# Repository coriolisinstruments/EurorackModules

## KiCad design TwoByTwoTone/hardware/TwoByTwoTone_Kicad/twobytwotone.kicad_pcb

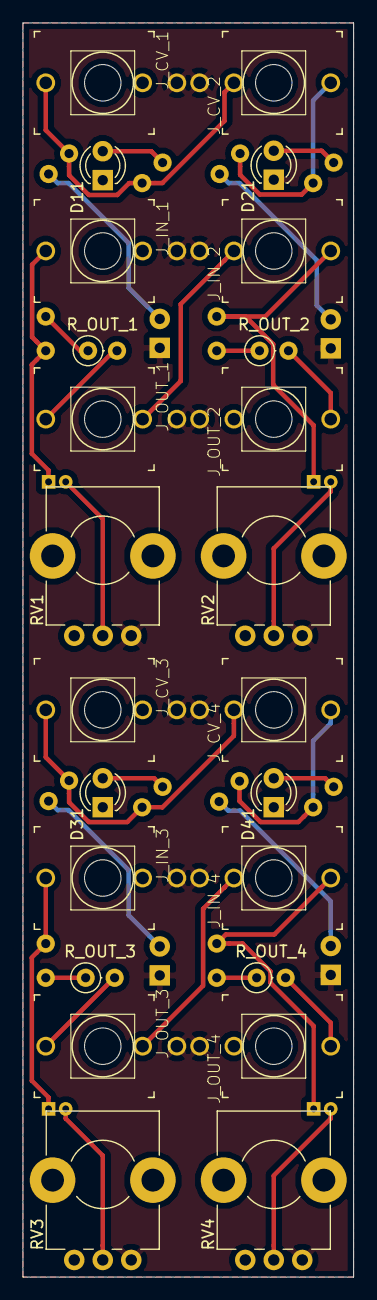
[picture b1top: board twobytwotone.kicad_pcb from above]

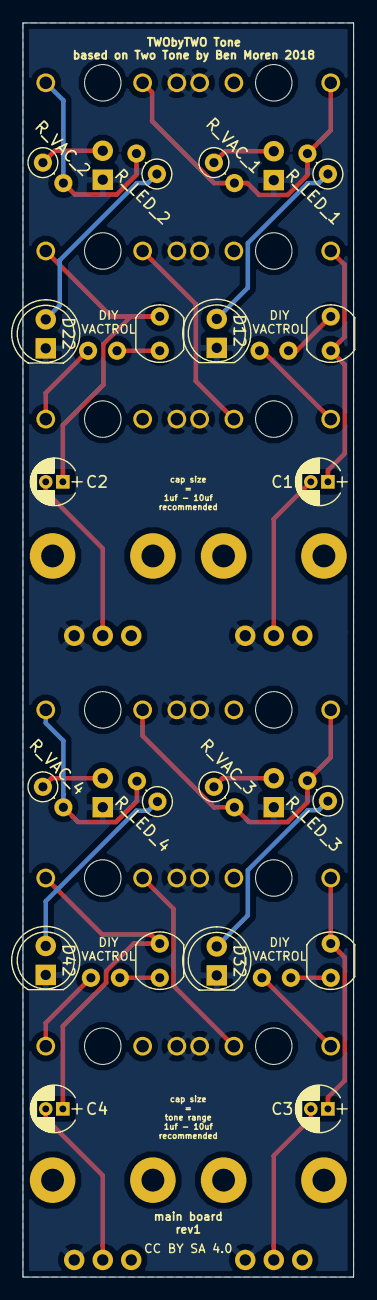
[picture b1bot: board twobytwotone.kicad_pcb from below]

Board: 2 copper layers, 29.0 x 110.0 mm, 44 parts (20 on the bottom side), 31 nets.

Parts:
C1, C2, C3, C4: 10uF; CP_Radial_D4.0mm_P1.50mm
D11, D21, D31, D41: LED; LED_D3.0mm
D12, D22, D32, D42: VAC-LED; LED_D5.0mm
J_CV_1, J_CV_2, J_CV_3, J_CV_4: thonkiconn; MusicThingModular-WQP-PJ301M-12_JACK
J_IN_1, J_IN_2, J_IN_3, J_IN_4: thonkiconn; MusicThingModular-WQP-PJ301M-12_JACK
J_OUT_1, J_OUT_2, J_OUT_3, J_OUT_4: thonkiconn; MusicThingModular-WQP-PJ301M-12_JACK
RV1, RV2, RV3, RV4: A10K; Potentiometer_Alps_RK09K_Horizontal
R_LED_1, R_LED_2, R_LED_3, R_LED_4: 20K; R_Axial_DIN0207_L6.3mm_D2.5mm_P2.54mm_Vertical
R_OUT_1, R_OUT_2, R_OUT_3, R_OUT_4: 1K; R_Axial_DIN0207_L6.3mm_D2.5mm_P2.54mm_Vertical
R_VAC_1, R_VAC_2, R_VAC_3, R_VAC_4: 20K; R_Axial_DIN0207_L6.3mm_D2.5mm_P2.54mm_Vertical
VAC-PHOTO1, VAC-PHOTO2, VAC-PHOTO3, VAC-PHOTO4: 45k-140k1; Resistor_LDR_5x4.1_RM3

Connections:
GND: D11.1, D12.1, D21.1, D22.1, D31.1, D32.1, D41.1, D42.1, J_CV_1.P$3_SLEEVE, J_CV_2.P$3_SLEEVE, J_CV_3.P$3_SLEEVE, J_CV_4.P$3_SLEEVE, J_IN_1.P$3_SLEEVE, J_IN_2.P$3_SLEEVE, J_IN_3.P$3_SLEEVE, J_IN_4.P$3_SLEEVE, J_OUT_1.P$3_SLEEVE, J_OUT_2.P$3_SLEEVE, J_OUT_3.P$3_SLEEVE, J_OUT_4.P$3_SLEEVE, RV1.1, RV2.1, RV3.1, RV4.1
unnamed: C1.1, J_IN_1.P$1_TIP, VAC-PHOTO1.1
unnamed: C1.2, RV1.2
unnamed: C2.1, J_IN_2.P$1_TIP, VAC-PHOTO2.2
unnamed: C2.2, RV2.2
unnamed: C3.1, J_IN_3.P$1_TIP, VAC-PHOTO3.2
unnamed: C3.2, RV3.2
unnamed: C4.1, J_IN_4.P$1_TIP, VAC-PHOTO4.2
unnamed: C4.2, RV4.2
unnamed: D11.2, R_VAC_1.1
unnamed: D12.2, R_LED_1.1
unnamed: D21.2, R_VAC_2.1
unnamed: D22.2, R_LED_2.1
unnamed: D31.2, R_VAC_3.1
unnamed: D32.2, R_LED_3.1
unnamed: D41.2, R_VAC_4.1
unnamed: D42.2, R_LED_4.1
unnamed: J_CV_1.P$1_TIP, J_CV_2.P$2_SWITCH, R_LED_1.2, R_VAC_1.2
unnamed: J_CV_2.P$1_TIP, R_LED_2.2, R_VAC_2.2
unnamed: J_CV_3.P$1_TIP, J_CV_4.P$2_SWITCH, R_LED_3.2, R_VAC_3.2
unnamed: J_CV_4.P$1_TIP, R_LED_4.2, R_VAC_4.2
unnamed: J_IN_2.P$2_SWITCH, J_OUT_1.P$2_SWITCH
unnamed: J_IN_4.P$2_SWITCH, J_OUT_3.P$2_SWITCH
unnamed: J_OUT_1.P$1_TIP, R_OUT_1.2
unnamed: J_OUT_2.P$1_TIP, R_OUT_2.2
unnamed: J_OUT_3.P$1_TIP, R_OUT_3.2
unnamed: J_OUT_4.P$1_TIP, R_OUT_4.2
unnamed: R_OUT_1.1, VAC-PHOTO1.2
unnamed: R_OUT_2.1, VAC-PHOTO2.1
unnamed: R_OUT_3.1, VAC-PHOTO3.1
unnamed: R_OUT_4.1, VAC-PHOTO4.1

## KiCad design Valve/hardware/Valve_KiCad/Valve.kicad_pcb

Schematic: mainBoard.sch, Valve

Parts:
C1, C2: 47nF; C_Rect_L7.0mm_W2.5mm_P5.00mm
C3, C4, C10: 10uF (25V); CP_Radial_D4.0mm_P2.00mm
C5, C6, C9: 100nF; C_Rect_L7.0mm_W2.5mm_P5.00mm
C7: 1uF (25V); CP_Radial_D4.0mm_P2.00mm
C8: 10nF; C_Rect_L7.0mm_W2.5mm_P5.00mm
D1, D2: IN4001; D_DO-41_SOD81_P10.16mm_Horizontal
D3, D4, D5: IN4148; D_DO-35_SOD27_P7.62mm_Horizontal
D6: LED; LED_D3.0mm
F1, F2: 72V/0.25A; Fuse_TE5_Littlefuse-395Series
J1, J3: Conn_02x05_Odd_Even; Pin_Header_Straight_2x05_Pitch2.54mm
J_IN1: Audio-Jack-2_Switch; WQP-PJ301M-12_JACK
J_OUT1: Audio-Jack-2_Switch; WQP-PJ301M-12_JACK
Q1: BC547; TO-92_Molded_Narrow
Q2: BC557; TO-92_Molded_Narrow
R1: 1M; R_Axial_DIN0207_L6.3mm_D2.5mm_P7.62mm_Horizontal
R2: 220K; R_Axial_DIN0207_L6.3mm_D2.5mm_P7.62mm_Horizontal
R3: 470K; R_Axial_DIN0207_L6.3mm_D2.5mm_P7.62mm_Horizontal
R4, R16: 100K; R_Axial_DIN0207_L6.3mm_D2.5mm_P7.62mm_Horizontal
R5, R7, R8, R14, R17: 10K; R_Axial_DIN0207_L6.3mm_D2.5mm_P7.62mm_Horizontal
R6: 150K; R_Axial_DIN0207_L6.3mm_D2.5mm_P7.62mm_Horizontal
R9: 1K; R_Axial_DIN0207_L6.3mm_D2.5mm_P7.62mm_Horizontal
R10, R11, R12, R13: 15K; R_Axial_DIN0207_L6.3mm_D2.5mm_P7.62mm_Horizontal
R15: 51K; R_Axial_DIN0207_L6.3mm_D2.5mm_P7.62mm_Horizontal
R18: 680r; R_Axial_DIN0207_L6.3mm_D2.5mm_P7.62mm_Horizontal
R19: 470r; R_Axial_DIN0207_L6.3mm_D2.5mm_P7.62mm_Horizontal
RV_DRIVE1: 100K; 9MM_SNAP-IN_POT
RV_DRYWET1: 10K; 9MM_SNAP-IN_POT
RV_FB1: 500K; 9MM_SNAP-IN_POT
RV_GAIN1: 10K; Potentiometer_Alps_RK09K_Horizontal
RV_TONE1: 100K; 9MM_SNAP-IN_POT
RV_VOL1: A100K; 9MM_SNAP-IN_POT
SW1: SW_SPDT; SUBMINI_TOGGLE
U1: TL074; DIP-14_W7.62mm_Socket

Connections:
/Main board/+12V: C3.1, C5.1, D3.2, F1.1, J3.9, Q1.1, R2.2, R4.2, U1.4 (V+)
/Main board/-12V: C4.2, C6.2, F2.1, J3.10, SW1.3, U1.11 (V-)
/Main board/CLEAN: R7.1, R10.2, U1.1
/Main board/GND: C3.2, C4.1, C5.2, C6.1, C10.2, D1.2, D2.1, J1.3, J1.4, J1.5, J1.6, J1.7, J1.8, J3.4, J3.5, J_IN1.2, J_OUT1.2, R6.1, R9.2, R16.1, R18.1, RV_DRYWET1.2, RV_TONE1.1, RV_TONE1.2, RV_VOL1.1, SW1.1, U1.3 (+), U1.5 (+)
/Main board/TUBE_1: C2.2, J3.1, R2.1
/Main board/TUBE_2: C1.1, J3.2, R1.2
/Main board/TUBE_3: J3.3, RV_DRIVE1.3
/Main board/TUBE_6: C7.1, J3.6, R4.1
/Main board/TUBE_7: C2.1, J3.7, R3.2
/Main board/TUBE_8: J3.8, R1.1, R3.1, RV_DRIVE1.1, RV_DRIVE1.2, SW1.2
/Main board/TUBE_IN: C1.2, C9.1, R8.1, U1.7
/Main board/TUBE_OUT: R11.2, R14.2, RV_FB1.1, RV_FB1.2, RV_GAIN1.2, RV_GAIN1.3, U1.8
unnamed: C7.2, C8.1, R6.2, U1.10 (+)
unnamed: C8.2, RV_TONE1.3
unnamed: C9.2, RV_FB1.3
unnamed: C10.1, Q1.3, R16.2, R17.2
unnamed: D1.1, F1.2, J1.9, J1.10
unnamed: D2.2, F2.2, J1.1, J1.2
unnamed: D3.1, D4.2
unnamed: D4.1, D5.2
unnamed: D5.1, D6.2, Q2.1
unnamed: D6.1, Q2.3, R18.2
unnamed: J_IN1.1, R5.2
unnamed: J_OUT1.1, R19.1
unnamed: Q1.2, R14.1
unnamed: Q2.2, R17.1
unnamed: R5.1, R7.2, R8.2, U1.2 (-), U1.6 (-)
unnamed: R9.1, RV_GAIN1.1, U1.9 (-)
unnamed: R10.1, R12.2, RV_DRYWET1.1
unnamed: R11.1, R13.2, RV_DRYWET1.3
unnamed: R12.1, R13.1, U1.13 (-)
unnamed: R15.1, RV_VOL1.3, U1.14
unnamed: R15.2, U1.12 (+)
unnamed: R19.2, RV_VOL1.2

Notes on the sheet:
Reverse polarity protection with input power buffers. (If not required, omit diodes and replace fuses with jumper wire. Don't get it the wrong way around~)
Powersupply
Connection to tube board
OVERVIEW
After-tube gain circuit Gain = 1 + (R7/R6) ie. now limited to 1+(10k/1k) = 11 = 20.8 dB
TUBE OVERDRIVE
Clipping indicator
For a LED with 2V/20ma, R >= 560r
Plate voltage switch This switches the ground of the tube section (grid drain+cathode) to 1) Up = -12V for 24V Vp or 2) Down = GND for regular 12V Vp
high-pass: f = 1/(2pi*R1*C1) = 1/(6.28*470k*47n*) = 7.2 Hz
3=up

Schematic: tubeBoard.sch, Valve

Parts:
J2: Conn_01x03_Male; Pin_Header_Straight_1x03_Pitch2.54mm
J4: Conn_02x05_Odd_Even; Pin_Header_Straight_2x05_Pitch2.54mm
RFBB1: POT_TRIM; Potentiometer_Trimmer_Bourns_3296W
RFBT1: 150r; R_Axial_DIN0207_L6.3mm_D2.5mm_P7.62mm_Horizontal
SX1: VT9-PT; belton-engineering-VT9-PT
U2: LM337_TO220; TO-220-3_Vertical

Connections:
/Tube Board/+12V_TB: J4.9
/Tube Board/-6.3V_TB: J2.3, RFBT1.2, U2.3
/Tube Board/-12V_TB: J2.1, J4.10, U2.2
/Tube Board/GND_TB: J4.4, J4.5, RFBB1.1, RFBB1.2, SX1.5
/Tube Board/TUBE_1_TB: J4.1, SX1.1
/Tube Board/TUBE_2_TB: J4.2, SX1.2
/Tube Board/TUBE_3_TB: J4.3, SX1.3
/Tube Board/TUBE_4_TB: J2.2, SX1.4
/Tube Board/TUBE_6_TB: J4.6, SX1.6
/Tube Board/TUBE_7_TB: J4.7, SX1.7
/Tube Board/TUBE_8_TB: J4.8, SX1.8
unnamed: RFBB1.3, RFBT1.1, U2.1

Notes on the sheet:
Connection to main board
For different tubes switch between 1) 12V (12A*7) and 3) 6.3V (6N2H) Note we use the -12V rail to balance some of the power consumption in typical a eurorack system. Hence the reversal of the connections to pin 4 and 5.
Vout = -1.25*((RFBB/RFBT) + 1) or Rfbb = Rfbt*((Vout/-1.25)-1) in our case: Rfbb = 150*((-6.25/-1.25)-1)=900r

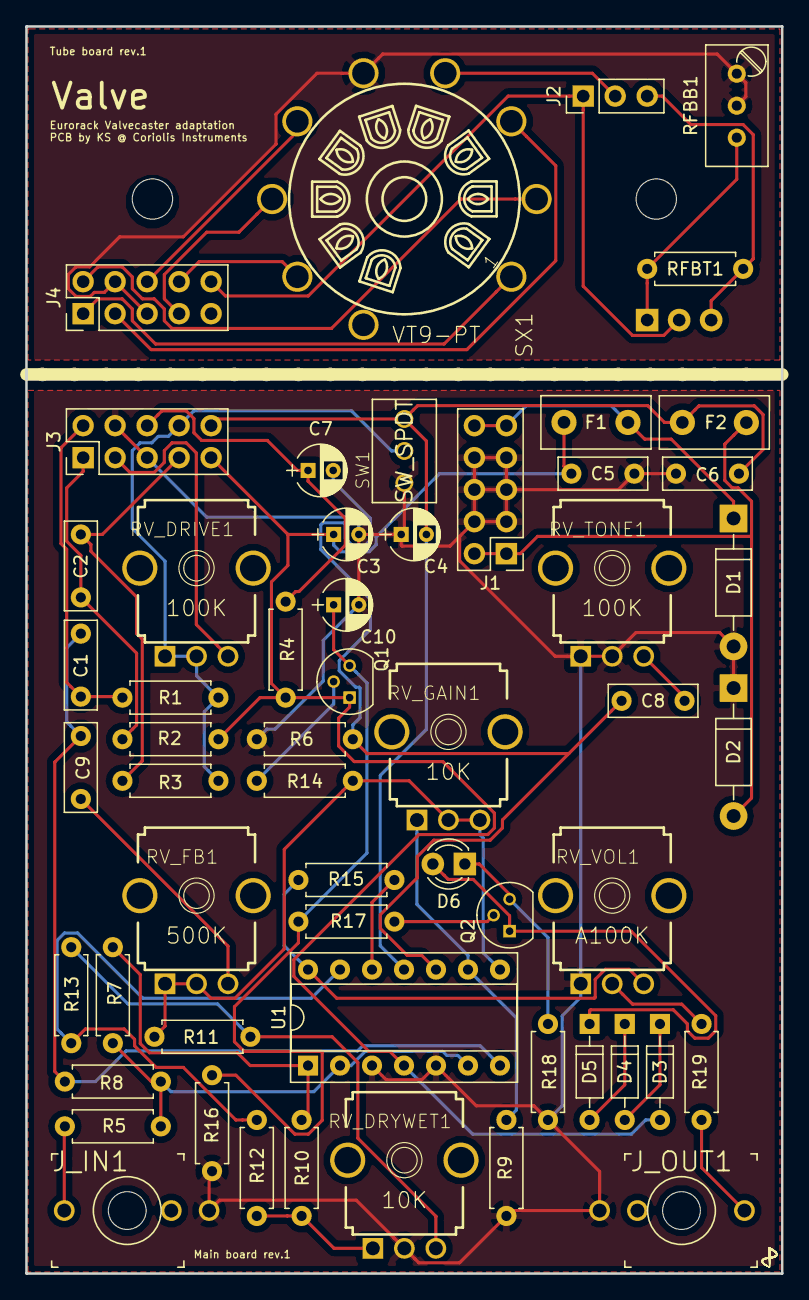
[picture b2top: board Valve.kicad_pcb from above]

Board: 2 copper layers, 60.0 x 99.0 mm, 57 parts (1 on the bottom side), 45 nets.

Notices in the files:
TwoByTwoTone/hardware/TwoByTwoTone_Kicad/twobytwotone.kicad_pcb:
CC BY SA 4.0
